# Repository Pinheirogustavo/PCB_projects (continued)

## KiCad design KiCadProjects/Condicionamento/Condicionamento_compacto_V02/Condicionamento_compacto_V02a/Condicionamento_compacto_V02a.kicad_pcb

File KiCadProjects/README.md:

# Versao do CAD: KiCad 7.0    

Placa 900x100mm face dupla

## Dicas gerais de uso do KiCad

- Os projetos desenvolvidos na versão Kicad 7.0 não são compatíveis com versões mais recentes.

- Sempre que for alterar um projeto abra o "arquivo_pro" específico, não o arquivo geral "KiCadProjects.kicad_pro".

- Ao realizar alguma modificação de projeto elétrico (não somente design), Faça a alteração no arquivo esquemático "arquivo_sch" e depois altere o arquivo de design "arquivo_pcb" por meio da ferramenta de "atualize a PCI com as alterações feitas no esquema - F8" (símbolo no painel superior). Modificações realizadas no sentido contrário não são atualizadas no esquema e assim sua placa confeccionada não irá corresponder ao projeto elétrico criado.

- Um bom tutorial em vídeo pode ser encontrado na playlist: <https://youtube.com/playlist?list=PL3bNyZYHcRSUhUXUt51W6nKvxx2ORvUQB&si=-wXaexDJ6YDI0aJu>

- Ao criar os seus esquemas tente separar cada estágio ou módulo e evite realizar ligações diretas de "wire", pois isso irá deixar a leitura mais confusa. Ao invés disso, utilize "rótulos globais" (Ctrl L / etiqueta no painel direito), que funcionam como conectores e ainda indicam os nós dos circuitos.

## Criando simbolos, footprint e 3D  

- Editor de símbolos &rarr; Arquivo &rarr; Nova biblioteca &rarr; Global &rarr; acesse a pasta de bibliotecas do seu github &rarr; acesse a pasta dos simbolos criados por você &rarr; NOME_SIMBOLO.kicad_sym Salvar. 
 - clique em "Criar Novo Símbolo (N)" 
  
- Quando criar um novo simbolo procure seguir Reference designator: https://en.wikipedia.org/wiki/Reference_designator 
  
- Sempre utilize pinos passivos 
- Numere os pinos no desenho do símbolo, para que o footprint possa fazer a atribuição correta 
- Nome do simbolo: Duplo clique na area de trabalho &rarr; preencher o campo valor 

## Como adicionar bibliotecas  

- Bibliotecas prontas da internet (salvar em Projeto Global): https://forum.digikey.com/t/importing-the-digi-key-kicad-library-into-kicad-5-0-0/4075 
 caminho:/PCB_projects/KiCadProjects/libraries/ 
  
- Bibliotecas criadas pelo autor:  Usar o editor de simbolos e de footprint do kicad, salvar em Projeto Global.

    Caminho:/PCB_projects/KiCadProjects/libraries/MyCreates

    Já criados símbolos e footprints dos seguintes componentes:

        Módulo do gerador AD9833

        Módulo do gerador AD9850

        Módulo do Potenciômetro digital X9c10x

        Chave gangorra

- Sempre adicione as bibliotecas pelo github e não pela sua máquina local. Exemplo: 
    
 Errado: /home/name/PCB_projects/KiCadProjects/libraries/MyCreates/AD9833_module.pretty 
    
 Certo: /home/name/**github**/PCB_projects/KiCadProjects/libraries/MyCreates/AD9833_module.pretty 

 ###### Há nesse tutorial uma lista de footprints para os componentes mais comuns entre os circuitos. Utilize essa lista para garantir que haja espaço adequado a esses componentes em sua placa.

## Algumas das regras de layout PCB  - Fabricação JLCPCB

#### Todas as regras e restrições para a produção pela Jlcpcb devem ser conferidas em: <https://jlcpcb.com/capabilities/pcb-capabilities>

- largura dos segmentos de linha de corte ( Edge.cuts): 0.15 mm
  
- Tamanho de via: 0.30mm - 6.30mm diâmetro interno. Diâmetro externo deve ser no mínimo 0.20mm maior que o interno.

- Largura da trilha: mínimo de 0.16 mm (6.5 mils)

- Espaçamento entre trilhas: mínimo de 0.10 mm (4 mils)

- Espaçamento entre trilha e borda da via: mínimo de 0.10 mm (4 mils)

- Serigrafia: Largura mínima da linha de 0.16 mm (6 mils) e altura mínima do texto de 1.00 mm (40 mils).
    - Preferencialmente manter a proporção 1:6.

##### Todas essas restrições podem ser definidas por meio das "Regras de desenho" do Kicad.

 Símbolo de engrenagem (segundo no painel superior_ &rarr; Regras de desenho &rarr; tamanhos pré-definidos.
    - Permite estabelecer tamanhos de vias e trilhas que serão seguidas em todo o desenho.

 Símbolo de engrenagem (segundo no painel superior_ &rarr; Regras de desenho &rarr; restrições.
    - Permite estabalecer regras que se violadas serão indicadas pelo verificador de regras de desenho.

  Símbolo de engrenagem (segundo no painel superior_ &rarr; Texto & gráfico.
    - Permite estabelecer tamanho de Serigrafia que será seguido em todo o desenho.

##### Sempre execute o "Verificador de regras de desenho (símbolo de lista no painel superior) antes de gerar os arquivos para confecção.

- Extra: para produção na CNC - O grid deve ser maior que o diâmetro da fresa utilizada (>0,2mm).

## Orientações para layout PCB  

- Criar trilhas de alimentação, de terra e de clock. 
- Fazer as trilhas de alimentação com largura maior 
- Evitar trilhas muito longas 
- Preferir mudanças de direção de 45º nas trilhas 
- Evitar que trilhas de sinais críticos (clock e altas freqüências) fiquem paralelas por muito tempo 
- Evitar ligações diretas entre as entradas de alimentação de Cis 
- Colocar um LED indicando que a placa está energizada 
- Colocar pontos de acesso para medir com o osciloscópio 
- Usar soquetes para os CIs 
 
- Segundo ícone, ao lado do simbolo de disquete. Serve para editar as regras de furos, tamanhos de trilhas... sempre conferir. 
  
- Ícone de lista. Serve para verificar as regras RDC. 

## Alguns footprints de componentes comuns   

Resistor
    
    Resistor_THT:R_Axial_DIN0207_L6.3mm_D2.5mm_P7.62mm_Horizontal 

Capacitor eletrolítico
    
    Capacitor_THT:CP_Radial_D5.0mm_P2.50mm 

Capacitor cerâmico 
    
    Capacitor_THT:C_Disc_D3.0mm_W1.6mm_P2.50mm

Capacitor tântalo 
    
    Capacitor_THT:CP_Radial_Tantal_D4.5mm_P2.50mm 

Diodo
    
    Diode_THT:D_DO-41_SOD81_P10.16mm_Horizontal

LED 
    
    LED_THT:LED_D5.0mm 

conectores fêmea

    Connector_PinSocket_2.54mm:PinSocket_1xXX_P2.54mm_Vertical 

conectores macho 
   
    Connector_PinHeader_2.54mm:PinHeader_1xXX_P2.54mm_Vertical 

conector p4 de bateria 
    
    Connector_BarrelJack:BarrelJack_GCT_DCJ200-10-A_Horizontal 

chave gangorra
    
    Chave_Gangorra:chave gangorra 2 pinos
    
L7809
    
    Package_TO_SOT_THT:TO-220-3_Vertical
    
LM7909
    
    Package_TO_SOT_THT:TO-220-3_Vertical
    
LM675
    
    Package_TO_SOT_THT:TO-220-5_P3.4x3.7mm_StaggerOdd_Lead3.8mm_Vertical
    
L7805
    
    Package_TO_SOT_THT:TO-220-3_Vertical
    
L7905
    
    Package_TO_SOT_THT:TO-220-3_Vertical
    
LM1117T-3.3
    
    Package_TO_SOT_THT:TO-220-3_Vertical
    
AD9850
    
    Capacitor_THT:C_Disc_D3.0mm_W1.6mm_P2.50mm
    
STM32-bluepill
    
    BluePill_STM32:BluePill_STM32F103C
    
AD828
    
    AD828:AD828
    
Potenciômetro Digital X9c10x
    
    X9c10X_module:X9c10X_module
    
Arduino Nano
    
    Module:Arduino_Nano
    
AD9833
    
    AD9833_module:AD9833_module

## Tamanho de pad de componentes comuns   

###### Caso esteja usando a CNC, todos os furos podem ser configurados diretamente no FlatCAM, não sendo necessário defini-los no projeto do Kicad.

- Resistores 

>Forma da ilha: Oval
>
>Tamanho da ilha: 2,0x1,6mm
>
>Forma do furo: circular
>
>Diâmetro do furo: 0,8mm

- Capacitores eletrolíticos 

> Forma da ilha: oval(+)            retangular(-)
>
> Tamanho da ilha:2,0x1,6mm(+)      2,0x1,6mm(-)
>
> Forma do furo: circular(+)        circular(-)
>
> Diâmetro do furo: 0,8mm(+)        0,8mm(-)

- Diodos 

> Forma da ilha: oval(+)            retangular(-)
>
> Tamanho da ilha:2,0x1,6mm(+)      2,0x1,6mm(-)
>
> Forma do furo: circular(+)        circular(-)
>
> Diâmetro do furo: 0,8mm(+)        0,8mm(-) 

- LED 

> Forma da ilha: oval(+)            retangular(-)
>
> Tamanho da ilha:2,0x1,8mm(+)      1,8x1,8mm(-)
>
> Forma do furo: circular(+)        circular(-)
>
> Diâmetro do furo: 1,1mm(+)        1,1mm(-) 

- Barra de pinos 

> Forma da ilha: oval
>
> Tamanho da ilha: 2,5x1,8mm
>
> Forma do furo:circular
>
> Diâmetro do furo: 1,02
  
- Chave gangorra

> Forma da ilha: Retangular
>
> Tamanho da ilha: 2,5x7,0mm
>
> Forma do furo: oval
>
> Diâmetro do furo: 0,8x6,0mm

- Conector p4 de bateria 

    - pad1 (vin)
    
        > Forma da ilha: retangular
	
        > Tamanho da ilha: 4,6x2,0mm
	
        > Forma do furo: oval
	
        > Diâmetro do furo: 3,6x1,0mm_P2
        
    - pad2 (vee)
    
        > Forma da ilha: Oval
	
        > Tamanho da ilha: 4,2x2,0mm
	
        > Forma do furo: oval
	
        > Diâmetro do furo: 3,2x1,0mm
        
    - pad3
    
        > Forma da ilha: Oval
	
        > Tamanho da ilha: 2,0x4,2mm
	
        > Forma do furo: oval
	
        > Diâmetro do furo: 1,0x3,2mm

## Autoroteamento

-   Utilize o plugin Freerouting ou Grid Router
-   Antes de tudo sempre realize primeiramente a atualiação da PCB a partir do esquemático e a verifcação das regras de desenho
-   Caso deseje refazer o roteamento, exclua todas as trilhas e vias geradas anteriormente: Editar → Exclusões globais → Vias e trilhas/Todas as camadas.
-   Caso tenha criado uma “zona” (linha tracejada) para o plano terra, a remova antes de realizar novo Autoroteamento (Ver mais em:  [https://www.reddit.com/r/KiCad/comments/5eu7fo/freerouting_left_a_lot_of_grounds_unreachable/](https://www.reddit.com/r/KiCad/comments/5eu7fo/freerouting_left_a_lot_of_grounds_unreachable/))

## Envio para produção no JLCPCB

#### Todas as orientações para a produção pela Jlcpcb a partir do Kicad 7.0 devem ser conferidas em: <https://jlcpcb.com/help/article/how-to-generate-gerber-and-drill-files-in-kicad-7>

Em resumo, você deve gerar 3 tipos de arquivos: Gerber, de perfuração (drill) e o mapeamento do projeto.

- Gerar arquivos Gerber: Files &rarr; Fabrication outputs &rarr; Gerbers (.gbr)
    As seguintes camadas devem ser selecionadas:

        F.Cu

        F.Paste

        F.Silks

        F.Mask

        B.Cu

        B.Paste

        B.Silks

        B.Mask

        Edge.Cuts

imagem retirada do site da JLCPCB

- Para gerar os arquivos de furo clique em "generate drill files" e siga as instruções:

imagem retirada do site da JLCPCB

- Gere o arquivo de mapeamento clicando em "generate Map file".

- Todos os arquivos devem ser salvos em única pasta.

- Ao final a pasta deve conter 13 arquivos que são enviados para produção em .ZIP ou .RAR a partir da página inicial da fabricante.

#### Como produzir placas pequenas de modo repetido (Painel)

O tamanho mínimo das placas confeccionadas na JLCPCB é de 100x100mm. Caso a placa produzida seja menor, é possível copiar o design dentro de uma área definida. Há dois modos de realizar isso:

- Por meio do próprio site de encomenda do circuito. Em "PCB Specifications" selecione "Panel by JLCPCB". Ele irá captar as dimensões das linhas de "Edge.cuts" do projeto e assim você só precisa selecionar o número de linhas e colunas com repetição do projeto.

- Manualmente: Há um plugin, "Kikit", que auxilia esse trabalho. Uma vez instalado o circuito pode ser repetido por n linhas e m colunas com o uso da ferramenta "Kikit: Panelize PCB".

###### No momento de escrita desse tutorial não havia diferença de preço entre os modos de "panelização".

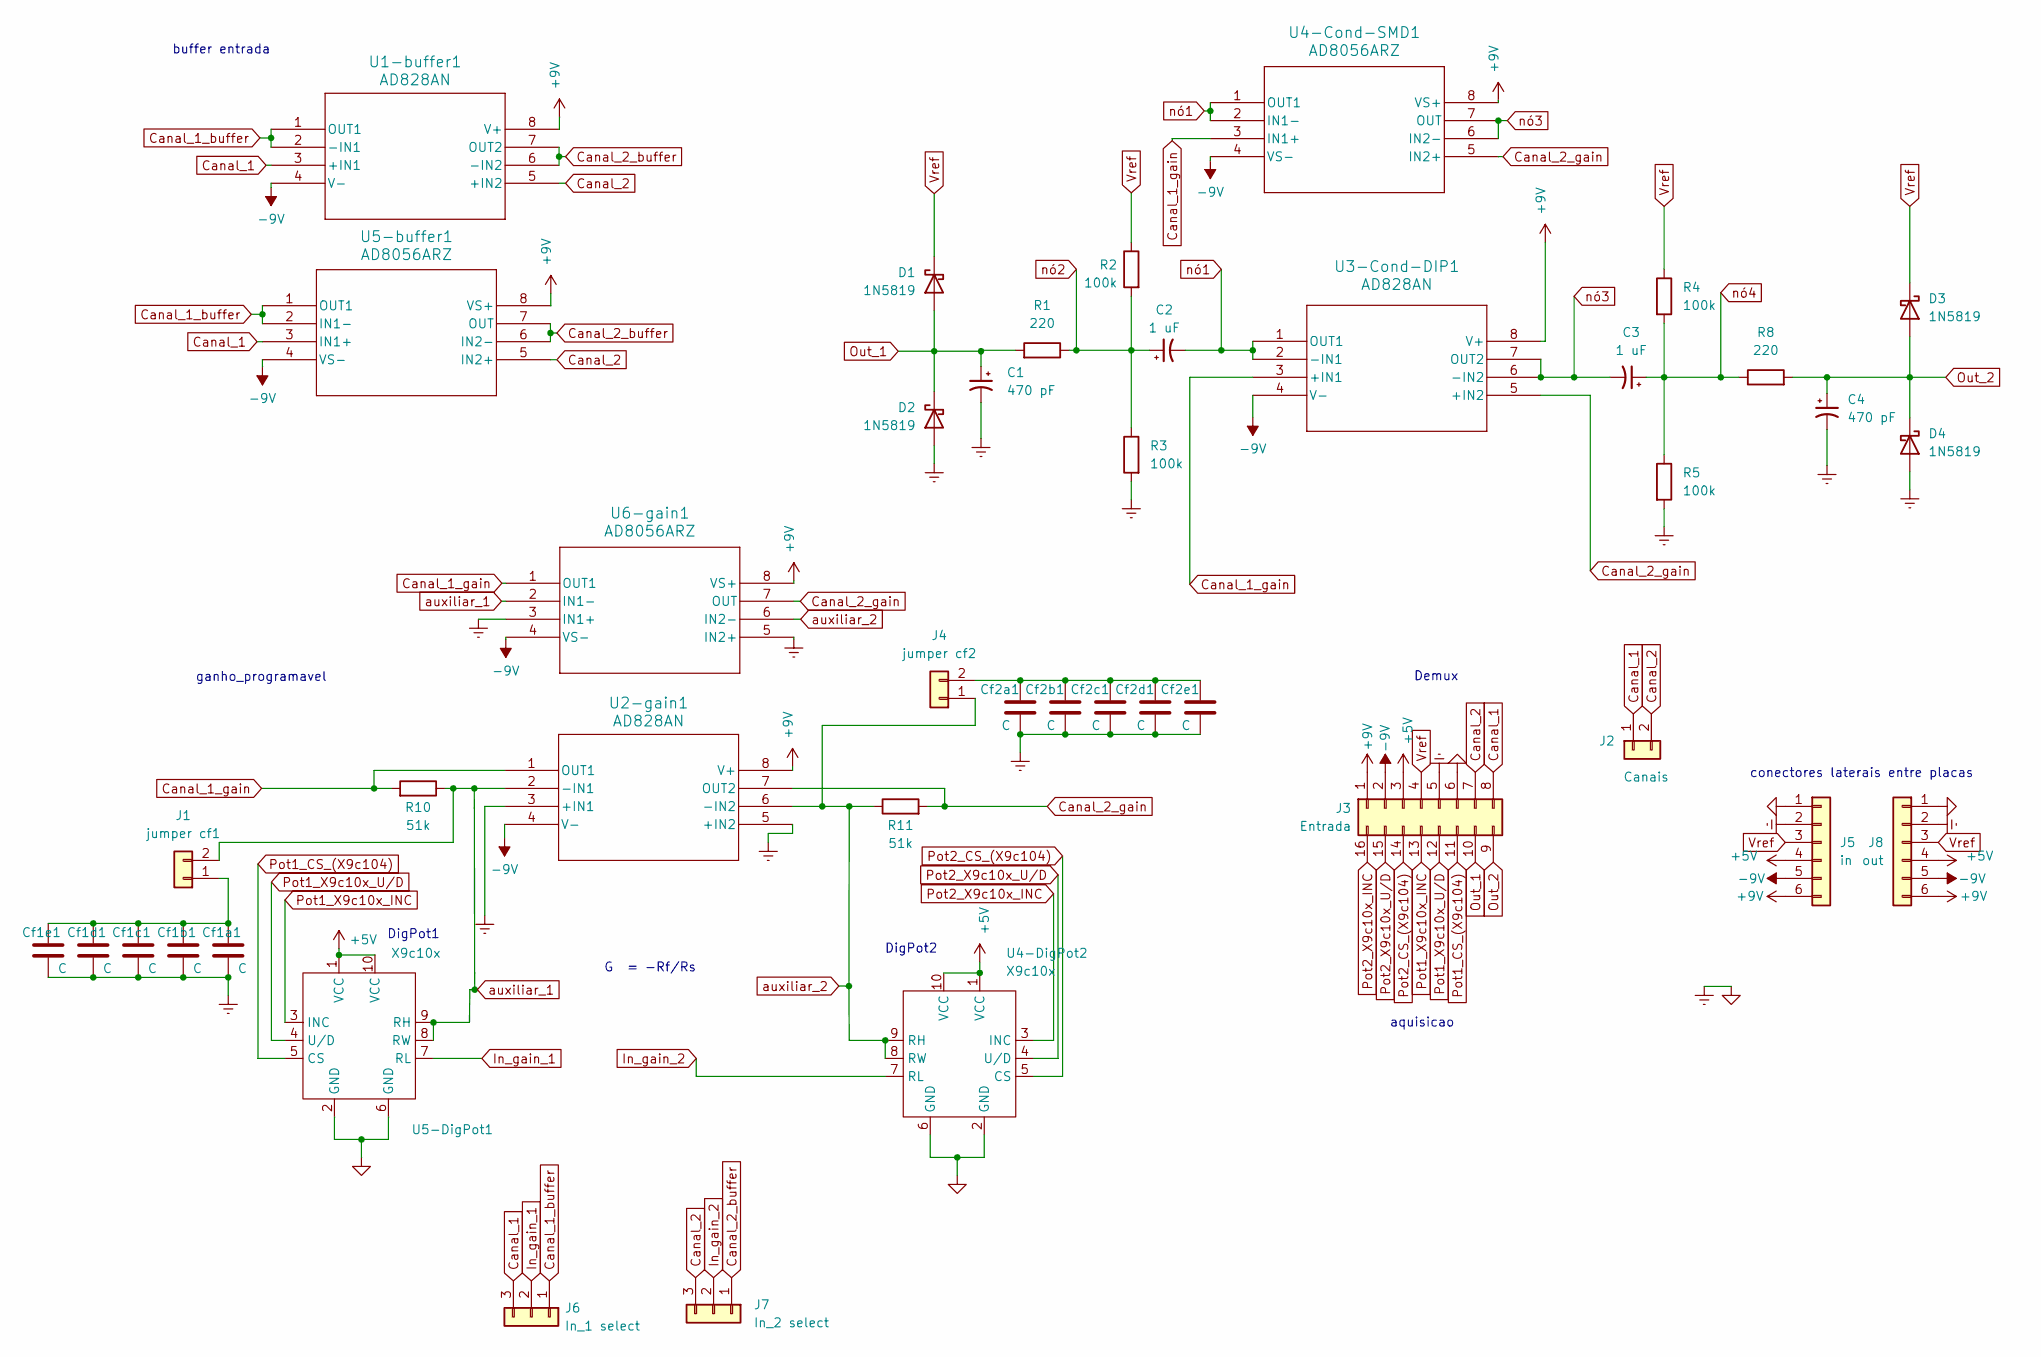
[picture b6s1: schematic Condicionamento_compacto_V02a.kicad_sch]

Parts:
C1, C4: 470 pF; CP_Radial_D5.0mm_P2.50mm
C2, C3: 1 uF; CP_Radial_D5.0mm_P2.50mm
Cf1a1, Cf1b1, Cf1c1, Cf1d1, Cf1e1, Cf2a1, Cf2b1, Cf2c1, Cf2d1, Cf2e1: C; CP_Radial_D5.0mm_P2.50mm
D1, D2, D3, D4: 1N5819; D_DO-41_SOD81_P10.16mm_Horizontal
J1: jumper cf1; PinHeader_1x02_P2.54mm_Vertical
J2: Canais; PinHeader_1x02_P2.54mm_Vertical
J3: Entrada; PinHeader_2x08_P2.54mm_Horizontal
J4: jumper cf2; PinHeader_1x06_P2.54mm_Horizontal
J5: in; PinSocket_1x06_P2.54mm_Horizontal
J6: In_1 select; PinHeader_1x03_P2.54mm_Vertical
J7: In_2 select; PinHeader_1x03_P2.54mm_Vertical
J8: out; PinHeader_1x06_P2.54mm_Horizontal
R1, R8: 220; R_Axial_DIN0207_L6.3mm_D2.5mm_P7.62mm_Horizontal
R2, R3, R4, R5: 100k; R_Axial_DIN0207_L6.3mm_D2.5mm_P7.62mm_Horizontal
R10, R11: 51k; R_Axial_DIN0207_L6.3mm_D2.5mm_P7.62mm_Horizontal
U1-buffer1, U2-gain1, U3-Cond-DIP1: AD828AN; N_8_ADI
U4-Cond-SMD1, U5-buffer1, U6-gain1: AD8056ARZ; R_8_ADI
U4-DigPot2, U5-DigPot1: X9c10x; X9c10X_module

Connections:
+5V: J3.3, J5.4, J8.4, U4-DigPot2.1 (VCC), U4-DigPot2.10 (VCC), U5-DigPot1.1 (VCC), U5-DigPot1.10 (VCC)
+9V: J3.1, J5.6, J8.6, U1-buffer1.8 (V+), U2-gain1.8 (V+), U3-Cond-DIP1.8 (V+), U4-Cond-SMD1.8 (VS+), U5-buffer1.8 (VS+), U6-gain1.8 (VS+)
-9V: J3.2, J5.5, J8.5, U1-buffer1.4 (V-), U2-gain1.4 (V-), U3-Cond-DIP1.4 (V-), U4-Cond-SMD1.4 (VS-), U5-buffer1.4 (VS-), U6-gain1.4 (VS-)
Canal_1: J2.1, J3.8, J6.3, U1-buffer1.3 (+IN1), U5-buffer1.3 (IN1+)
Canal_1_buffer: J6.1, U1-buffer1.1 (OUT1), U1-buffer1.2 (-IN1), U5-buffer1.1 (OUT1), U5-buffer1.2 (IN1-)
Canal_1_gain: R10.2, U2-gain1.1 (OUT1), U3-Cond-DIP1.3 (+IN1), U4-Cond-SMD1.3 (IN1+), U6-gain1.1 (OUT1)
Canal_2: J2.2, J3.7, J7.3, U1-buffer1.5 (+IN2), U5-buffer1.5 (IN2+)
Canal_2_buffer: J7.1, U1-buffer1.6 (-IN2), U1-buffer1.7 (OUT2), U5-buffer1.6 (IN2-), U5-buffer1.7 (OUT)
Canal_2_gain: R11.2, U2-gain1.7 (OUT2), U3-Cond-DIP1.5 (+IN2), U4-Cond-SMD1.5 (IN2+), U6-gain1.7 (OUT)
Earth: C1.2, C4.2, Cf1a1.2, Cf1b1.2, Cf1c1.2, Cf1d1.2, Cf1e1.2, Cf2a1.2, Cf2b1.2, Cf2c1.2, Cf2d1.2, Cf2e1.2, D2.2 (A), D4.2 (A), J3.5, J3.6, J5.1, J5.2, J8.1, J8.2, R3.2, R5.2, U2-gain1.3 (+IN1), U2-gain1.5 (+IN2), U4-DigPot2.2 (GND), U4-DigPot2.6 (GND), U5-DigPot1.2 (GND), U5-DigPot1.6 (GND), U6-gain1.3 (IN1+), U6-gain1.5 (IN2+)
In_gain_1: J6.2, U5-DigPot1.7 (RL)
In_gain_2: J7.2, U4-DigPot2.7 (RL)
unnamed: Cf1a1.1, Cf1b1.1, Cf1c1.1, Cf1d1.1, Cf1e1.1, J1.1
unnamed: Cf2a1.1, Cf2b1.1, Cf2c1.1, Cf2d1.1, Cf2e1.1, J4.2
Out_1: C1.1, D1.2 (A), D2.1 (K), J3.10, R1.2
Out_2: C4.1, D3.2 (A), D4.1 (K), J3.9, R8.2
Pot1_CS_(X9c104): J3.11, U5-DigPot1.5 (CS)
Pot1_X9c10x_INC: J3.13, U5-DigPot1.3 (INC)
Pot1_X9c10x_U/D: J3.12, U5-DigPot1.4 (U/D)
Pot2_CS_(X9c104): J3.14, U4-DigPot2.5 (CS)
Pot2_X9c10x_INC: J3.16, U4-DigPot2.3 (INC)
Pot2_X9c10x_U/D: J3.15, U4-DigPot2.4 (U/D)
Vref: D1.1 (K), D3.1 (K), J3.4, J5.3, J8.3, R2.1, R4.1
auxiliar_1: J1.2, R10.1, U2-gain1.2 (-IN1), U5-DigPot1.8 (RW), U5-DigPot1.9 (RH), U6-gain1.2 (IN1-)
auxiliar_2: J4.1, R11.1, U2-gain1.6 (-IN2), U4-DigPot2.8 (RW), U4-DigPot2.9 (RH), U6-gain1.6 (IN2-)
nó1: C2.2, U3-Cond-DIP1.1 (OUT1), U3-Cond-DIP1.2 (-IN1), U4-Cond-SMD1.1 (OUT1), U4-Cond-SMD1.2 (IN1-)
nó2: C2.1, R1.1, R2.2, R3.1
nó3: C3.2, U3-Cond-DIP1.6 (-IN2), U3-Cond-DIP1.7 (OUT2), U4-Cond-SMD1.6 (IN2-), U4-Cond-SMD1.7 (OUT)
nó4: C3.1, R4.2, R5.1, R8.1

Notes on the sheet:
DigPot2
Demux
G = -Rf/Rs
conectores laterais entre placas
aquisicao
ganho_programavel
buffer entrada
DigPot1

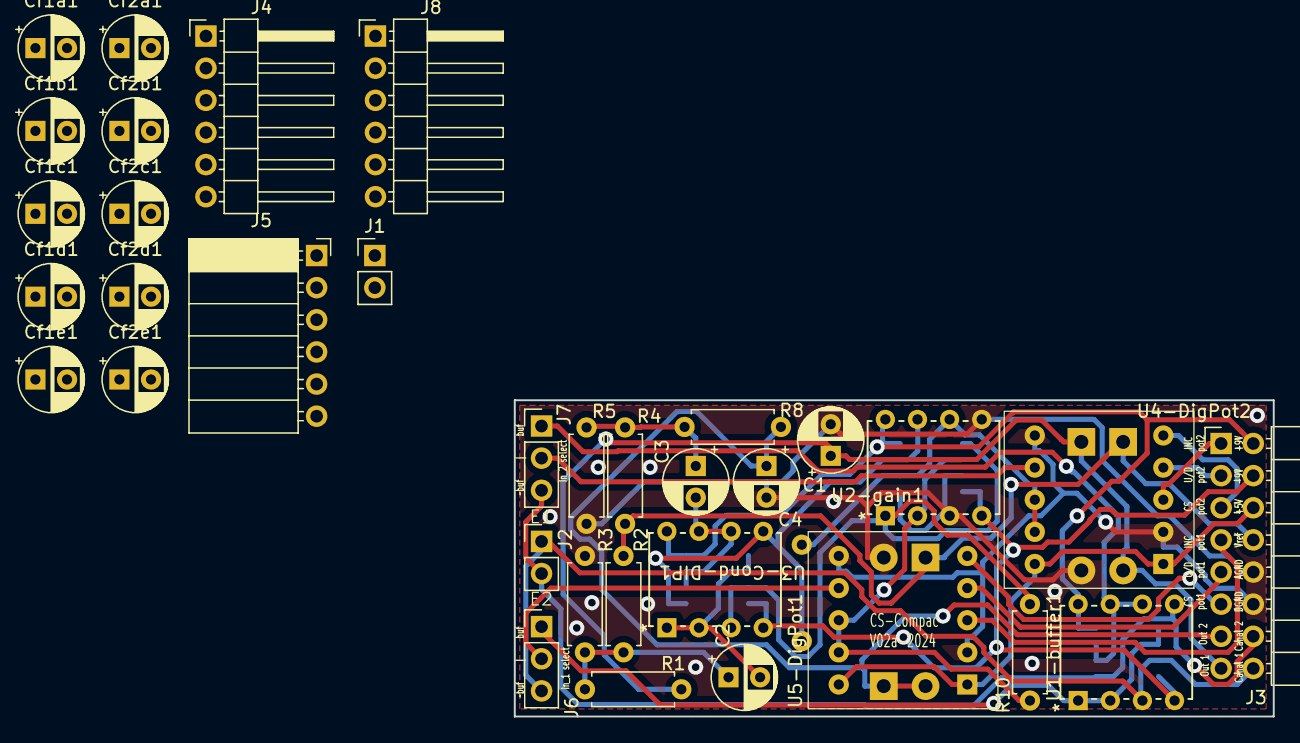
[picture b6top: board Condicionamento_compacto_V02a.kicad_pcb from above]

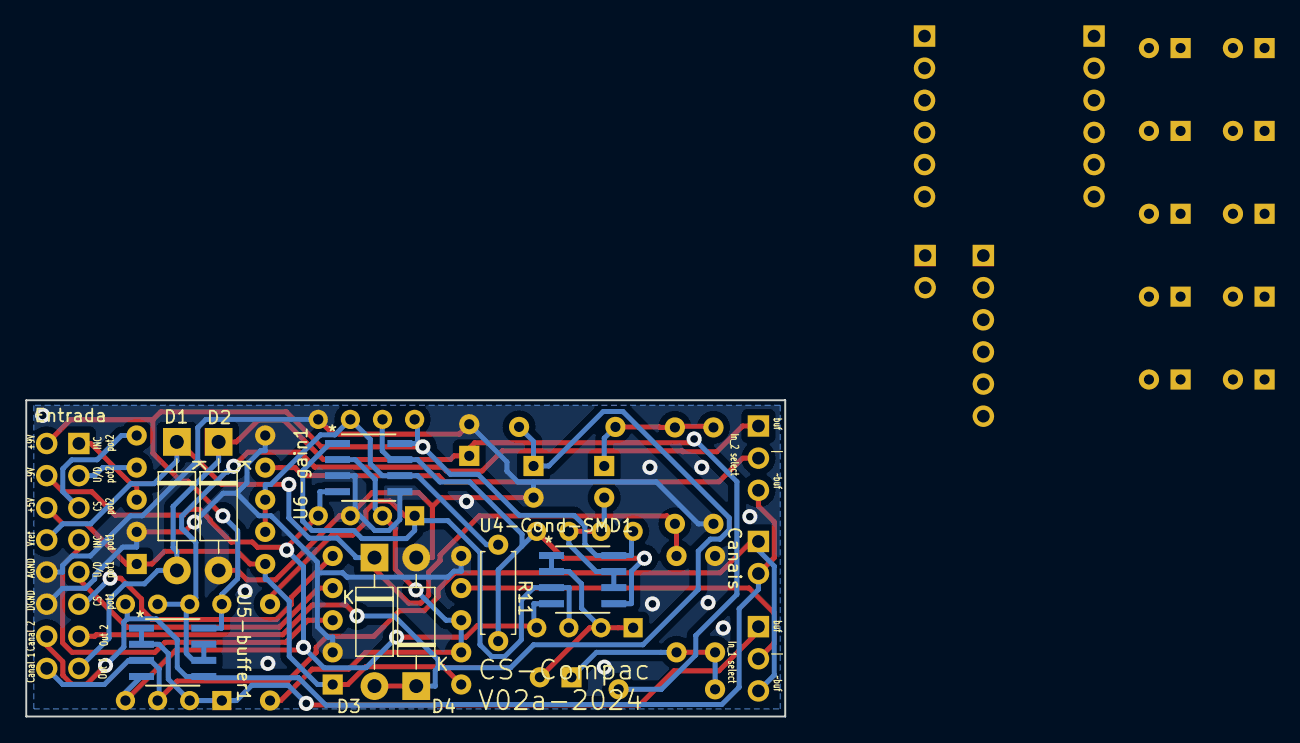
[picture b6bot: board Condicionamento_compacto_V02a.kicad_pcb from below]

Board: 2 copper layers, 60.0 x 25.0 mm, 42 parts (8 on the bottom side), 29 nets.

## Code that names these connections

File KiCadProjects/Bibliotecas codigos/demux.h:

/*
 * Funções para uso da placa demux "Demux.V02" de 16 canais do tomografo
 * Autor: Gustavo Pinheiro
 */

//Sinais de selecao dos mux que controlam a injecao de corrente
#define A_S0 PB5 //LSB
#define A_S1 PB4
#define A_S2 PB3
#define A_S3 PA15
#define A_S4 PB9 // MSB

//Sinais de selecao dos mux que controlam a drenagem de corrente
#define B_S0 PB15 //LSB
#define B_S1 PB14
#define B_S2 PB13
#define B_S3 PB12
#define B_S4 PB8 // MSB


//Sinais de enable dos mux que controlam a injecao de corrente
#define Enable_A  PA4
#define Enable_A1 PC15
#define Enable_A2 PA0
#define Enable_A3 PA1
#define Enable_A4 PA2

//Sinais de enable dos mux que controlam a drenagem de corrente
#define Enable_B  PA8
#define Enable_B1 PB0
#define Enable_B2 PB1
#define Enable_B3 PB10
#define Enable_B4 PB11


// Funcao para acionar determinado eletrodo de injecao de corrente
    //A partir do numero desse eletrodo (0-127)
void seleciona_canal_in(int canal){
  prepara_mux_in();
  //canais iniciam no num 0
  byte A = bitRead(canal,0); //LSB canal
  byte B = bitRead(canal,1);
  byte C = bitRead(canal,2);
  byte D = bitRead(canal,3);
  byte E = bitRead(canal,4); //MSB canal

  Serial.print("canal ");
  Serial.println(canal);
  Serial.print(A);
  Serial.print(B);
  Serial.print(C);
  Serial.print(D);
  Serial.println(E);

  digitalWrite(A_S0, A); // B5
  digitalWrite(A_S1, B); // B4
  digitalWrite(A_S2, C); // B3
  digitalWrite(A_S3, D); // A15
  digitalWrite(A_S4, E); // B9

  if (canal<8){ // liga apenas o mux A1
      digitalWrite(Enable_A1,0);
  } else if(canal<16){ //liga apenas o mux A2
      digitalWrite(Enable_A2,0);
  } else if(canal<24){ //liga apenas o mux A3
      digitalWrite(Enable_A3,0);
  } else if(canal<32){ //liga apenas o mux A4
      digitalWrite(Enable_A4,0);
  }
}

// Funcao para acionar determinado eletrodo de drenagem de corrente
    //A partir do numero desse eletrodo (128-255)
void seleciona_canal_out(int canal){
  prepara_mux_out();
  //canais iniciam no num 0
  int A = bitRead(canal,0); //LSB canal
  int B = bitRead(canal,1);
  int C = bitRead(canal,2);
  int D = bitRead(canal,3);
  int E = bitRead(canal,4); //MSB canal

  Serial.print("canal ");
  Serial.println(canal);
  Serial.print(A);
  Serial.print(B);
  Serial.print(C);
  Serial.print(D);
  Serial.println(E);

  digitalWrite(B_S0, A);
  digitalWrite(B_S1, B);
  digitalWrite(B_S2, C);
  digitalWrite(B_S3, D);
  digitalWrite(B_S4, E);

  if (canal<8){ //liga apenas o mux B1
      digitalWrite(Enable_B1,0);
    } else if(canal<16){ //liga apenas o mux B2
      digitalWrite(Enable_B2,0);
    } else if(canal<24){ //liga apenas o mux B3
      digitalWrite(Enable_B3,0);
    } else if(canal<32){ //liga apenas o mux B4
      digitalWrite(Enable_B,0);
    }
}

//Funcao define a GPIO do uC relacionada com controle do mux
void configura_pinos_mux(){
  // Variaveis de seleção do Mux
  //IN current
  pinMode(A_S0, OUTPUT);
  pinMode(A_S1, OUTPUT);
  pinMode(A_S2, OUTPUT);
  pinMode(A_S3, OUTPUT);
  pinMode(A_S4, OUTPUT);
  //OUT current
  pinMode(B_S0, OUTPUT);
  pinMode(B_S1, OUTPUT);
  pinMode(B_S2, OUTPUT);
  pinMode(B_S3, OUTPUT);
  pinMode(B_S4, OUTPUT);

  //  Variaveis de Habilitação do MUX IN (Nivel logico baixo)
  pinMode(Enable_A1, OUTPUT); //  MUX 1 "Eletrodo 0 a 7"
  pinMode(Enable_A2, OUTPUT); //  MUX 2 "Eletrodo 8 a 15"
  pinMode(Enable_A3, OUTPUT); //  MUX 3 "Eletrodo 16 a 23"
  pinMode(Enable_A4, OUTPUT); //  MUX 4 "Eletrodo 24 a 31"
  pinMode(Enable_A, OUTPUT);  //  MUX 5  primeiro da cascata
  //  Variaveis de Habilitação do MUX OUT (Nivel logico baixo)
  pinMode(Enable_B1, OUTPUT); //  MUX 1 "Eletrodo 0 a 7"
  pinMode(Enable_B2, OUTPUT); //  MUX 2 "Eletrodo 8 a 15"
  pinMode(Enable_B3, OUTPUT); //  MUX 3 "Eletrodo 16 a 23"
  pinMode(Enable_B4, OUTPUT); //  MUX 4 "Eletrodo 24 a 31"
  pinMode(Enable_B, OUTPUT);  //  MUX 5  primeiro da cascata
}

// Funcao que desliga todos os mux's relacionados com a injecao de corrente
void prepara_mux_in(){
  digitalWrite(Enable_A1, HIGH);  // MUX 1  desabilitado
  digitalWrite(Enable_A2, HIGH);  // MUX 2  desabilitado
  digitalWrite(Enable_A3, HIGH);  // MUX 3  desabilitado
  digitalWrite(Enable_A4, HIGH);  // MUX 4  desabilitado
  digitalWrite(Enable_A, LOW);    // MUX 5  habilitado, primeiro da cascata
}

// Funcao que desliga todos os mux's relacionados com a drenagem de corrente
void prepara_mux_out(){
  digitalWrite(Enable_B1, HIGH);  // MUX 1  desabilitado
  digitalWrite(Enable_B2, HIGH);  // MUX 2  desabilitado
  digitalWrite(Enable_B3, HIGH);  // MUX 3  desabilitado
  digitalWrite(Enable_B4, HIGH);  // MUX 4  desabilitado
  digitalWrite(Enable_B, LOW);    // MUX 5 habilitado, primeiro da cascata
}

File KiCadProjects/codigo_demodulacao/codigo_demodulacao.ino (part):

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uint16_t datav2[NUM_SAMPLES_MAX+1];

// O STM32F103 possui 10 pinos do ADC disponíveis:
// pino A0 (PA0) -> 0 (ADC0)
// ...
// pino A7 (PA7) -> 7 (ADC7)
// pino B0 (PB0) -> 8 (ADC8)
// pino B1 (PB1) -> 9 (ADC9)
// Para "dobrar" taxa de amostragem (FAST_INTERLEAVED true), medir o mesmo canal dos 2 ADCs.

//uint8 ADC1_Sequence[]={8,0,0,0,0,0};   // ADC1 channels sequence, left to right. Unused values must be 0. Note that these are ADC /channels, not pins
//uint8 ADC2_Sequence[]={9,0,0,0,0,0};   // ADC2 channels sequence, left to right. Unused values must be 0

// CASO 1: lê canal X e amplitude I1
uint8 ADC1_Sequence[]={0,0,0,0,0,0}; //PA0 sign_Cn
uint8 ADC2_Sequence[]={1,0,0,0,0,0}; //PA1 Ampl1


// CASO 2: lê canal X e canal Y
/*  uint8 ADC1_Sequence[]={0,0,0,0,0,0}; //PA0 sign_Cn
 *  uint8 ADC2_Sequence[]={8,0,0,0,0,0}; //PB0 sign_Cn+4
 */

// CASO 3: lê canal X e amplitude I2
/*  uint8 ADC1_Sequence[]={0,0,0,0,0,0}; //PA0 sign_Cn
 *  uint8 ADC2_Sequence[]={8,0,0,0,0,0}; //PA4 Ampl2
 */


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
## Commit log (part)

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2023-09-19 Versao do programa calibrado para o sistema com as placas antigas
2023-09-19 Versao do programa para as placas modulares, não calibrado
2023-09-19 versoes antigas
2023-09-20 versao torre, nao calibrado
2023-09-20 versao modular, nao calibrado
2023-09-20 funcao de calibracao
2023-09-20 verifica a subtracao das impedancias medidas nos canais 1 e 2
2023-09-22 versao sendo alterada
2023-09-27 mudanca nome variavel
2023-10-10 versao sendo atualizada
2023-10-11 calibracao da fase
2023-10-11 linha 179 master - segunda verificacao da fase
2023-10-11 comando p imprime os valores considerados na media de Z1
2023-10-11 correcao de fase em dft.h
2023-10-16 Ajuste fase soma 'phase1/2' master
2023-10-16 Ajuste fase soma 'phase1/2' slave
2023-10-16 dados voluntarios validacao da fase
2023-10-16 versao estavel - media da amplitude e fase
2023-10-16 mudanca impressao dos dados
2023-10-23 versao estavel
2023-10-23 retangular
2023-10-30 calculos validos (retangular)
2023-10-30 nova versao estavel
2023-10-30 voluntarios andre e luis
2023-10-31 dados voluntarios 1-4
2023-10-31 dados voluntarios 5 e 6
2023-11-01 novos voluntarios
2023-11-01 dados 20 voluntarios
2023-11-01 21 e 22
2023-11-01 voluntarios 26
2023-11-01 voluntario 27
2023-11-06 analise dos dados
2023-11-08 analise de FFM dos voluntarios
2023-11-12 temp
2023-11-18 resultados
2024-02-05 barramento utilizado na fonte de tensao V05/2023
2024-02-05 Readme
2024-02-05 primeira versao do gerador - TG
2024-02-05 Versao para o barramento V04/2024
2024-02-05 adicionar as bibliotecas atraves do github
2024-02-05 versao para barramento v04
2024-02-07 mudanca do barramento para a versao V04
2024-02-07 versao TG
2024-02-07 baseado barramento v04
2024-02-07 baseado no barramento v04
2024-02-08 Baseado barramento v04 - Finalizado
2024-02-16 Baseado barramento v04 - Finalizado - plano terra alternativo
2024-02-29 datasheets geradores
2024-02-29 mudanca pasta
2024-02-29 Orientacoes autoroteamento
2024-02-29 mudança AmpOp n inversor
2024-03-06 Atualizacao orientacao para criar componentes
2024-03-06 novo componente: ad9850 modulo
2024-03-06 atualizacao distancia pinos
2024-03-06 atualizacao valor
2024-03-06 atualizacao como adicionar nome ao simbolo
2024-03-06 Gerador baseado em ad9850 NAO FINALIZADO
2024-04-05 Descrição gerador ad9850
2024-04-05 Ataulizacao restricoes producao
2024-04-05 mudanca freq corte
2024-04-05 mudanca sinais de entrada e largura trilha
2024-04-05 Descrição circuito
2024-04-05 todas conexoes feitas
2024-04-05 Atualizacao restricoes producao
2024-04-05 particularidades da placa - tamanhos de trilhas, vias e pads
2024-04-05 documentacao
2024-04-05 Sistema proposto para controle de ganho de sinal
2024-04-06 esquematico
2024-04-10 Baseado barramento v04 - Finalizado - mudanca valor resitor leds
2024-04-10 fonte bipolar incial
2024-04-11 i2c - implementacao i2cBus
2024-04-11 Baseado barramento v04 - Finalizado - remocao resistor pullup i2c
2024-04-11 Baseado barramento v04 - Finalizado - implementacao resistor pullup i2c 2
2024-04-11 AVISO - BARRAMENTO DESATUALIZADO
2024-04-12 modelo 3d ad828
2024-06-05 V03 em producao - Compacto em projeto
2024-06-05 V05b:stepDown - V05:edgecuts 0.15mm
2024-06-05 add AD8056 LM2596 TL072
2024-06-05 projeto HeartLab
2024-06-05 em producao
2024-06-05 Fonte corrente compacta + condicionamento
2024-06-05 V01aCopia: menor, com vias. V01a: maior, sem vias
2024-06-06 print
2024-06-06 print esquematico
2024-06-11 demux - primeira versao
2024-06-12 placa de aquisicao para ser utilizada no barramento
2024-06-12 mudanca conectores
2024-06-13 enviar para producao
2024-06-13 add biblioteca mux 74HC4051 Dip16 model N
2024-06-13 modificar
2024-07-15 guias de montagem
2024-07-19 novos valores resistores LEDs
2024-07-20 mudanca footprint
2024-07-20 atualizacao guia montagem
2024-07-24 para producao
2024-07-25 mudanca de tamanho - enviado para producao
2024-07-26 lista de materiais
2024-07-26 guia de montagem
2024-07-26 programacao
2024-07-30 programa base ad9833
2024-07-31 biblioteca ad9833
2024-08-01 sinais
2024-08-07 biblioteca ad9850
2024-08-07 entradas e saidas
2024-08-07 programa controle serial
2024-08-07 entradas e saidas stm
2024-08-07 programa serial
2024-08-07 nome errado
2024-08-08 biblioteca encoder
2024-10-10 Imagens para tutorial kicad
2024-10-10 como usar o kicad
2024-10-16 datasheets mux
2024-10-16 encoder
2024-10-21 gerador
2024-10-22 programa controle mux
2024-10-22 programa controle aquisicao
2024-10-23 codigo
2024-10-23 codigos teste 23/10/24
2024-10-31 debug
2024-11-04 funciona
2024-11-05 teste
2024-11-05 versao com biblioteca
2024-11-06 verificar uso da biblioteca de dft - perguntas sinalizadas por ???
2024-11-13 correcao ativacao muxs
2024-11-14 versao backup codigo funcionando
2024-11-14 permitir rastrear qual versao da biblioteca esta sendo usada no projeto
2024-11-14 backup
2024-11-18 biblioteca AD8056
2024-11-19 backup funcionando
2024-11-26 circuito de controle de ganho por digipot
2024-11-27 esquema mudanca sistema ganho
2024-11-27 circuito de controle de ganho por digpot
2024-12-04 controle por chave
2024-12-05 datasheet chave cd4066
2024-12-05 programa controle chave
2024-12-07 circuito paralelo
2024-12-07 circuito serie
2024-12-09 circuito ganho serie
2024-12-09 circuito ganho paralelo
2024-12-11 solucao passa baixa
2024-12-11 solucao passa faixa
2024-12-11 com funcoes
2024-12-11 selecao resistores
2024-12-11 funcoes implementadas
2024-12-13 fft ruido digpot placa ad9850 V01
2024-12-13 correcao modelo
2024-12-14 programa base
2024-12-14 biblioteca analise sinal pelo osciloscopio
2024-12-16 funcoes octave analise oscilocopio
2024-12-16 valor capacitor usado no teste
2024-12-16 capacitor 6.8n para correcao ruido 50k@tl072
2024-12-16 caracterizacao ruido adicionando capacitor de correcao
2024-12-18 NAO FINALIZADO
2024-12-18 dados para testes das funcoes
2024-12-18 programas de teste para implementar biblioteca
2024-12-18 programa para controle do gerador de sinais AD9850 V01
2024-12-18 remove
2024-12-18 biblioteca para o gerador AD9850 V01
2024-12-18 backup codigo eletrodo
2024-12-18 backup codigo gerador ad9850 V01
2024-12-18 biblioteca modulo ad9833
2024-12-20 teste com ad826 freq zero todos passos digpot
2024-12-20 testando uso da biblioteca pronta do digpot (nao confiavel)
2024-12-20 biblioteca para o gerador AD9850 V01 - add debug
2024-12-20 mesmo procedimento repetido mas com 10k samples no osciloscopio
2024-12-20 ad826 f250k programa gerador debug
2024-12-20 KiCadProjects/ ad826 f250k programa gerador debug
2024-12-20 mesmo procedimento 10ksamples
2024-12-20 remove dados de teste
2025-01-14 cad circuito controle ganho com chave
2025-01-14 tabela para escolha dos resistores do circuito ganho chave
2025-01-14 programa para controlar as chaves do sistema de ganho
2025-01-17 programa para controlar as chaves
2025-01-18 codigo usado para demodular testes finais digpot
2025-01-18 descricao dos arquivos da pasta
2025-01-18 codigo backup
2025-01-24 inclui debug
2025-01-24 biblioteca com uso de chave
2025-01-25 valores cir: implementados no prototipo; valores ods: idealizado
2025-02-13 caracterizacao ruido digpot
2025-02-13 teste antigo
2025-02-18 mudanca escala imagem e tamanho legenda
2025-02-18 compensacao por ganho
2025-02-18 Atualizando README
2025-02-18 codigo mestre
2025-02-25 placa em producao
2025-02-25 projeto ganho controlavel
2025-02-25 codigos
2025-02-25 comandos do programa
2025-02-25 correcao Vcc mux U5B1
2025-03-01 add esquematico do circuito
2025-03-01 atualizacao versao de fonte sendo usada
2025-03-01 biblioteca que concentra todos componentes utilizados no projeto
2025-03-11 versao digpot
2025-03-11 versao chave digital
2025-03-11 lib ad828
2025-03-11 versao simples sem ganho
2025-03-11 digpot version
2025-03-11 switch version
2025-03-11 rename english
2025-03-11 producao
2025-03-11 Update .gitignore
    allow zip for jlcpcb production
2025-03-13 placa perfurada para encaixe no barramento
2025-04-11 Atualizando projeto do DEMUX
    Verificado que para os MUX de entrada: U3A3 U4A4 e os de saída: U2B2, U3B3 e U4B4. Não estavam com os sinais se seleção de canais corretamente adicionados. Então, foram alterados esses sinais e verif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
2025-04-11 Adicao do codigo atualizado
    Nessa nova versao do código é possível:
    * Alterar os eletrodos através do serial do Arduino IDE e não apenas através do mestre;
    * Momentaneamente para que seja possível acionar o eletrodo 0 como entrada, o eletrodo que é acionado corresponde ao comando -1. Ou seja, para acionar o eletrodo 0 (como entrada) é enviado o comando 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
    * Alterado um trecho do código demux.h que estava para acionar digitalWrite(Enable_A,0); e deveria ser digitalWrite(Enable_A4,0);.
    * Criado um padrão de acio
2025-04-15 correcao vcc vee ina
2025-04-29 lista materiais
2025-07-07 anotacoes reuniao erick
2025-12-04 deleted
2025-12-04 library sparkfun
2026-01-31 removendo
2026-01-31 correcao sinais de selecao e add capacitores alimentacao
2026-06-16 softwares de integracao - versao 0 Mirela
2026-06-16 Softwares - versao 0 - Gustavo
2026-06-16 Corrigindo pasta
2026-06-16 correcao nome diretorio
2026-06-17 Limpando código e ajustando endereços
2026-06-18 Limpando código do mestre.
